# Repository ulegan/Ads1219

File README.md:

# Ads1219
A breakout board for the [ADS1219](https://www.ti.com/product/ADS1219) 24-bit AD-Converter.<br />
Size and pinout is the same as the popular ADS1x15 boards.
- Up to 1000Hz samplingrate
- Single or continuous conversion
- Single ended or differential inputs

pcb made with [KiCad](https://kicad.org/)

### Boards ordered from [OSHPARK](https://oshpark.com/)

### Diagramm 

If you want to use single-ended inputs, you should not use C6 and C7

### Libraries
I have written libraries for **C** and **Python** tested on a Raspberry-Pi

OM2220 wrote an [Arduino library](https://github.com/OM222O/ADS1219) for it <br />
and there is also one for [micropython](https://github.com/miketeachman/micropython-ads1219) that I have not tested yet.<br />

All libraries use the I²C-address 0x40 by default, so you have to connect the ADDR-Pin to GND, or use 0x41 in the constructor.

#### I²C-Addressing
The ADS1219 has two address-pins A0 and A1. <br />
A1 is always connected to GND, A0 has a pullup to VCC.<br />
So the I²C-ADDRESS defaults to 0x41. <br />
Four different addresses can be selected by connecting A0:

| ADDR connected to | Address |
| :---------------- |:-------:|
| GND               | 0x40    |
| VCC or open       | 0x41    |
| SDA               | 0x42    |
| SCL               | 0x43    |

```c++

```

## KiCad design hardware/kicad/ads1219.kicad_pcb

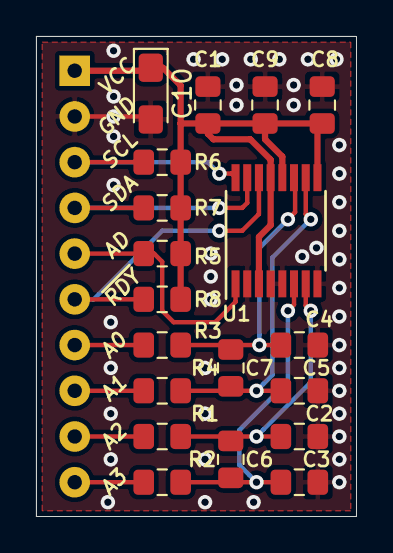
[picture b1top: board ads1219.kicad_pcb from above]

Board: 2 copper layers, 17.8 x 26.7 mm, 20 parts (1 on the bottom side), 14 nets.

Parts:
C1, C2, C3, C4, C5, C6, C7, C8, C9: 100n; C_0805_2012Metric_Pad1.15x1.40mm_HandSolder
C10: 10µ; CP_EIA-3216-10_Kemet-I_Pad1.58x1.35mm_HandSolder
J1: Conn_01x10; PinHeader_1x10_P2.54mm_Vertical
R1, R2, R3, R4, R5, R6, R7, R8: 10k; R_0805_2012Metric_Pad1.15x1.40mm_HandSolder
U1: ADS1219; TSSOP-16_4.4x5mm_P0.65mm

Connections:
/ADDR: J1.5, R5.1, U1.1
/AIN0: J1.7, R3.2
/AIN1: J1.8, R4.2
/AIN2: J1.9, R1.2
/AIN3: J1.10, R2.2
/SCL: J1.3, R6.1, U1.16
/SDA: J1.4, R7.1, U1.15
/~DRDY: J1.6, R8.1, U1.14
GND: C1.2, C2.2, C3.2, C4.2, C5.2, C8.2, C9.2, C10.2, J1.2, U1.2, U1.4, U1.5, U1.8
unnamed: C2.1, C6.1, R1.1, U1.7
unnamed: C3.1, C6.2, R2.1, U1.6
unnamed: C4.1, C7.1, R3.1, U1.11
unnamed: C5.1, C7.2, R4.1, U1.10
VCC: C1.1, C8.1, C9.1, C10.1, J1.1, R5.2, R6.2, R7.2, R8.2, U1.3, U1.9, U1.12, U1.13

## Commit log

2021-11-08 Update README.md
    https://forum.kicad.info/t/warning-avoid-all-links-to-kicad-pcb-org-use-kicad-org/31521
